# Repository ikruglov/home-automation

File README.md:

# Home automation · hardware & firmware

PCBs and ESPHome configurations for connecting existing appliances to Home Assistant.

Project records covering PCB design, firmware integration, and assembled hardware.

<table>
<tr>
<td width="45%">

</td>
<td valign="top">
<strong><a href="esp32-ap7921/">APC AP7921 controller retrofit</a></strong><br>
An installed and working replacement controller bringing eight-outlet control and monitoring into Home Assistant. An internal board swap retains the enclosure, outlet hardware, and front-panel layout.<br><br>
<sub>Four-layer PCB · ESP32-C6 · CH390H Ethernet · ESPHome</sub>
</td>
</tr>
<tr>
<td align="center">
<br>
<sub>PCB layout · Work in progress</sub>
</td>
<td valign="top">
<strong><a href="esp32-water-meter/">Water-meter reader</a></strong><br>
An ESP32-C6 water-meter reader with 18650 backup power to keep counting through USB power interruptions. Two sensor inputs support a planned approach to rejecting false counts from small target movements. Assembled and tested; current firmware uses Wi-Fi and one sensor.<br><br>
<sub>PCB design · ESP32-C6 · ESPHome · Battery backup · Dual sensor inputs</sub>
</td>
</tr>
<tr>
<td>

</td>
<td valign="top">
<strong><a href="esp32-create-ceiling-fan-tuya/">Create ceiling-fan retrofit</a></strong><br>
A replacement PCB with an ESP32-C3 module, support components, and programming connections, fitted to the original fan controller. ESPHome provides fan and light control over Tuya UART.<br><br>
<sub>PCB design · ESP32-C3 · Wi-Fi · Tuya UART</sub>
</td>
</tr>
<tr>
<td>

</td>
<td valign="top">
<strong><a href="esp32-climarad-v2x/">Climarad ventilation interface</a></strong><br>
A carrier PCB connecting existing Ethernet/PoE and isolated RS485 modules, with a printed enclosure and Modbus integration for Home Assistant.<br><br>
<sub>Carrier PCB · ESP32-S3 · Ethernet / PoE · RS485 / Modbus</sub>
</td>
</tr>
</table>

## Design decisions

| Project | Requirement | Approach | Boundary |
|---|---|---|---|
| AP7921 retrofit | Replace the controller and integrate outlet control and monitoring into Home Assistant | Four-layer controller PCB and ESPHome firmware, fitted to the existing enclosure and front panel | AP7921 mounting points and front-panel openings; USB-C replaces the serial connector |
| Water-meter reader (in progress) | Keep counting through power interruptions and reject false counts at the detection boundary | 18650 backup, two sensor inputs, and ESP32-C6 with a future Zigbee option | Assembled and tested; current firmware uses one sensor and Wi-Fi |
| Ceiling-fan retrofit | Expose the existing fan and light controls in Home Assistant | A custom ESP32-C3 board replaces the Wi-Fi interface and communicates with the retained controller over Tuya UART | Board fit and datapoint mappings are specific to the controller shown |
| Climarad interface | Connect ventilation controls and measurements to Home Assistant; power the interface through PoE | A custom carrier PCB combines Ethernet/PoE and isolated RS485 modules; ESPHome maps Modbus registers into entities | Uses the unit's Modbus interface and requires its device address |

All four projects use ESPHome's firmware framework and protocol components. The Climarad interface uses Waveshare modules for its ESP32, PoE, and isolated RS485 functions.

## Explore the projects

| Project | Hardware | Firmware | Additional material |
|---|---|---|---|
| [APC AP7921](esp32-ap7921/) | [Four-layer controller overview](esp32-ap7921/#four-layer-controller-pcb) | [ESPHome configuration and components](esp32-ap7921/firmware/) | [Installed retrofit](esp32-ap7921/#board-swap-retrofit) · [USB-C insert STL](esp32-ap7921/usb-c-insert.stl) |
| [Water-meter reader](esp32-water-meter/) | [KiCad design](esp32-water-meter/hardware/) | [ESPHome configuration](esp32-water-meter/firmware/) | [Case STL models](esp32-water-meter/case/) · [Development status](esp32-water-meter/#development-status) |
| [Create ceiling fan](esp32-create-ceiling-fan-tuya/) | [KiCad design](esp32-create-ceiling-fan-tuya/kicad/) | [ESPHome configuration](esp32-create-ceiling-fan-tuya/esphome.yaml) | [BOM](esp32-create-ceiling-fan-tuya/#bill-of-materials) · [Build gallery](esp32-create-ceiling-fan-tuya/#build-gallery) |
| [Climarad Sensa V2X](esp32-climarad-v2x/) | [KiCad design](esp32-climarad-v2x/kicad/) | [ESPHome configuration](esp32-climarad-v2x/esphome.yaml) | [Printable enclosure](esp32-climarad-v2x/case.3mf) |

These are hardware-specific project records. Read the compatibility and configuration notes before adapting a design to another appliance.

## License

- **Design files, documentation, and photographs:** [CC BY-NC 4.0](LICENSES/CC-BY-NC-4.0.txt).
- **Software and ESPHome configurations:** [PolyForm Noncommercial 1.0.0](LICENSES/PolyForm-Noncommercial-1.0.0.txt).

See [LICENSE](LICENSE) for scope.

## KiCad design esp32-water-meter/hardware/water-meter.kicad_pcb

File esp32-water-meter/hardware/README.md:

# Water-meter hardware

Open `water-meter.kicad_pro` with **KiCad 10** and matching standard libraries.
The schematic and PCB use file-format versions `20260306` and `20260206`.

Included:

- Schematic, PCB layout, and project settings.
- Project-local FS8205A and JLCImport symbols used by this design.
- Three JLCImport footprints and their referenced 3D models.
- Project-relative library tables and model paths.

The design also references **Espressif's `PCM_Espressif` library** for the
ESP32-C6 module. Install that library separately for library-based editing and
updates; placed symbols and footprints are embedded in the design files. Its
3D model currently uses the original `KICAD8_3RD_PARTY` variable. Configure that
variable for the installed library location, or update the model path locally.
Standard models use `KICAD10_3DMODEL_DIR`.

This export changes local library/model paths, not the circuit or routing.
The custom symbol library contains only the symbols needed here; unrelated
private-project libraries are excluded. Production outputs and editor state
are not included.

## Open work

The private design's TODO still lists **F1 value/selection** as unresolved.
The firmware development notes describe modifications to the sensor input
and USB power handling; reconcile those with the assembled revision before
using these files to build another board.

KiCad ERC/DRC and schematic-to-PCB agreement have not been checked for this
export. Regenerate manufacturing outputs only after reviewing the design.

## Protection-circuit references

The PCB's stored pad nets place Q6 (AO3401A, LCSC C347476) in the battery
positive connection, with its gate referenced to BAT−: the intended reverse
insertion protection stage. Q1 is a separate MOSFET in the USB/battery power
path. See the [Q6 datasheet](https://www.lcsc.com/datasheet/C347476.pdf).

U5 is labelled DW01A in the schematic and carries LCSC C686633. Its OD/OC
outputs drive Q5, the dual battery-disconnect MOSFET. The
[datasheet linked to C686633](https://www.lcsc.com/datasheet/C686633.pdf)
identifies the part as DW01 and documents overcharge, overdischarge,
overcurrent, and short-circuit detection. Confirm the fitted variant before
relying on specific thresholds; no thresholds are claimed on the project page.

F1 is a resettable fuse in the battery-positive path. USBLC6 protection and
SMAJ12A TVS devices are also present at the external interfaces/sensor supply.
Protection functions are identified from the design; fault performance has not
been independently verified for this export.

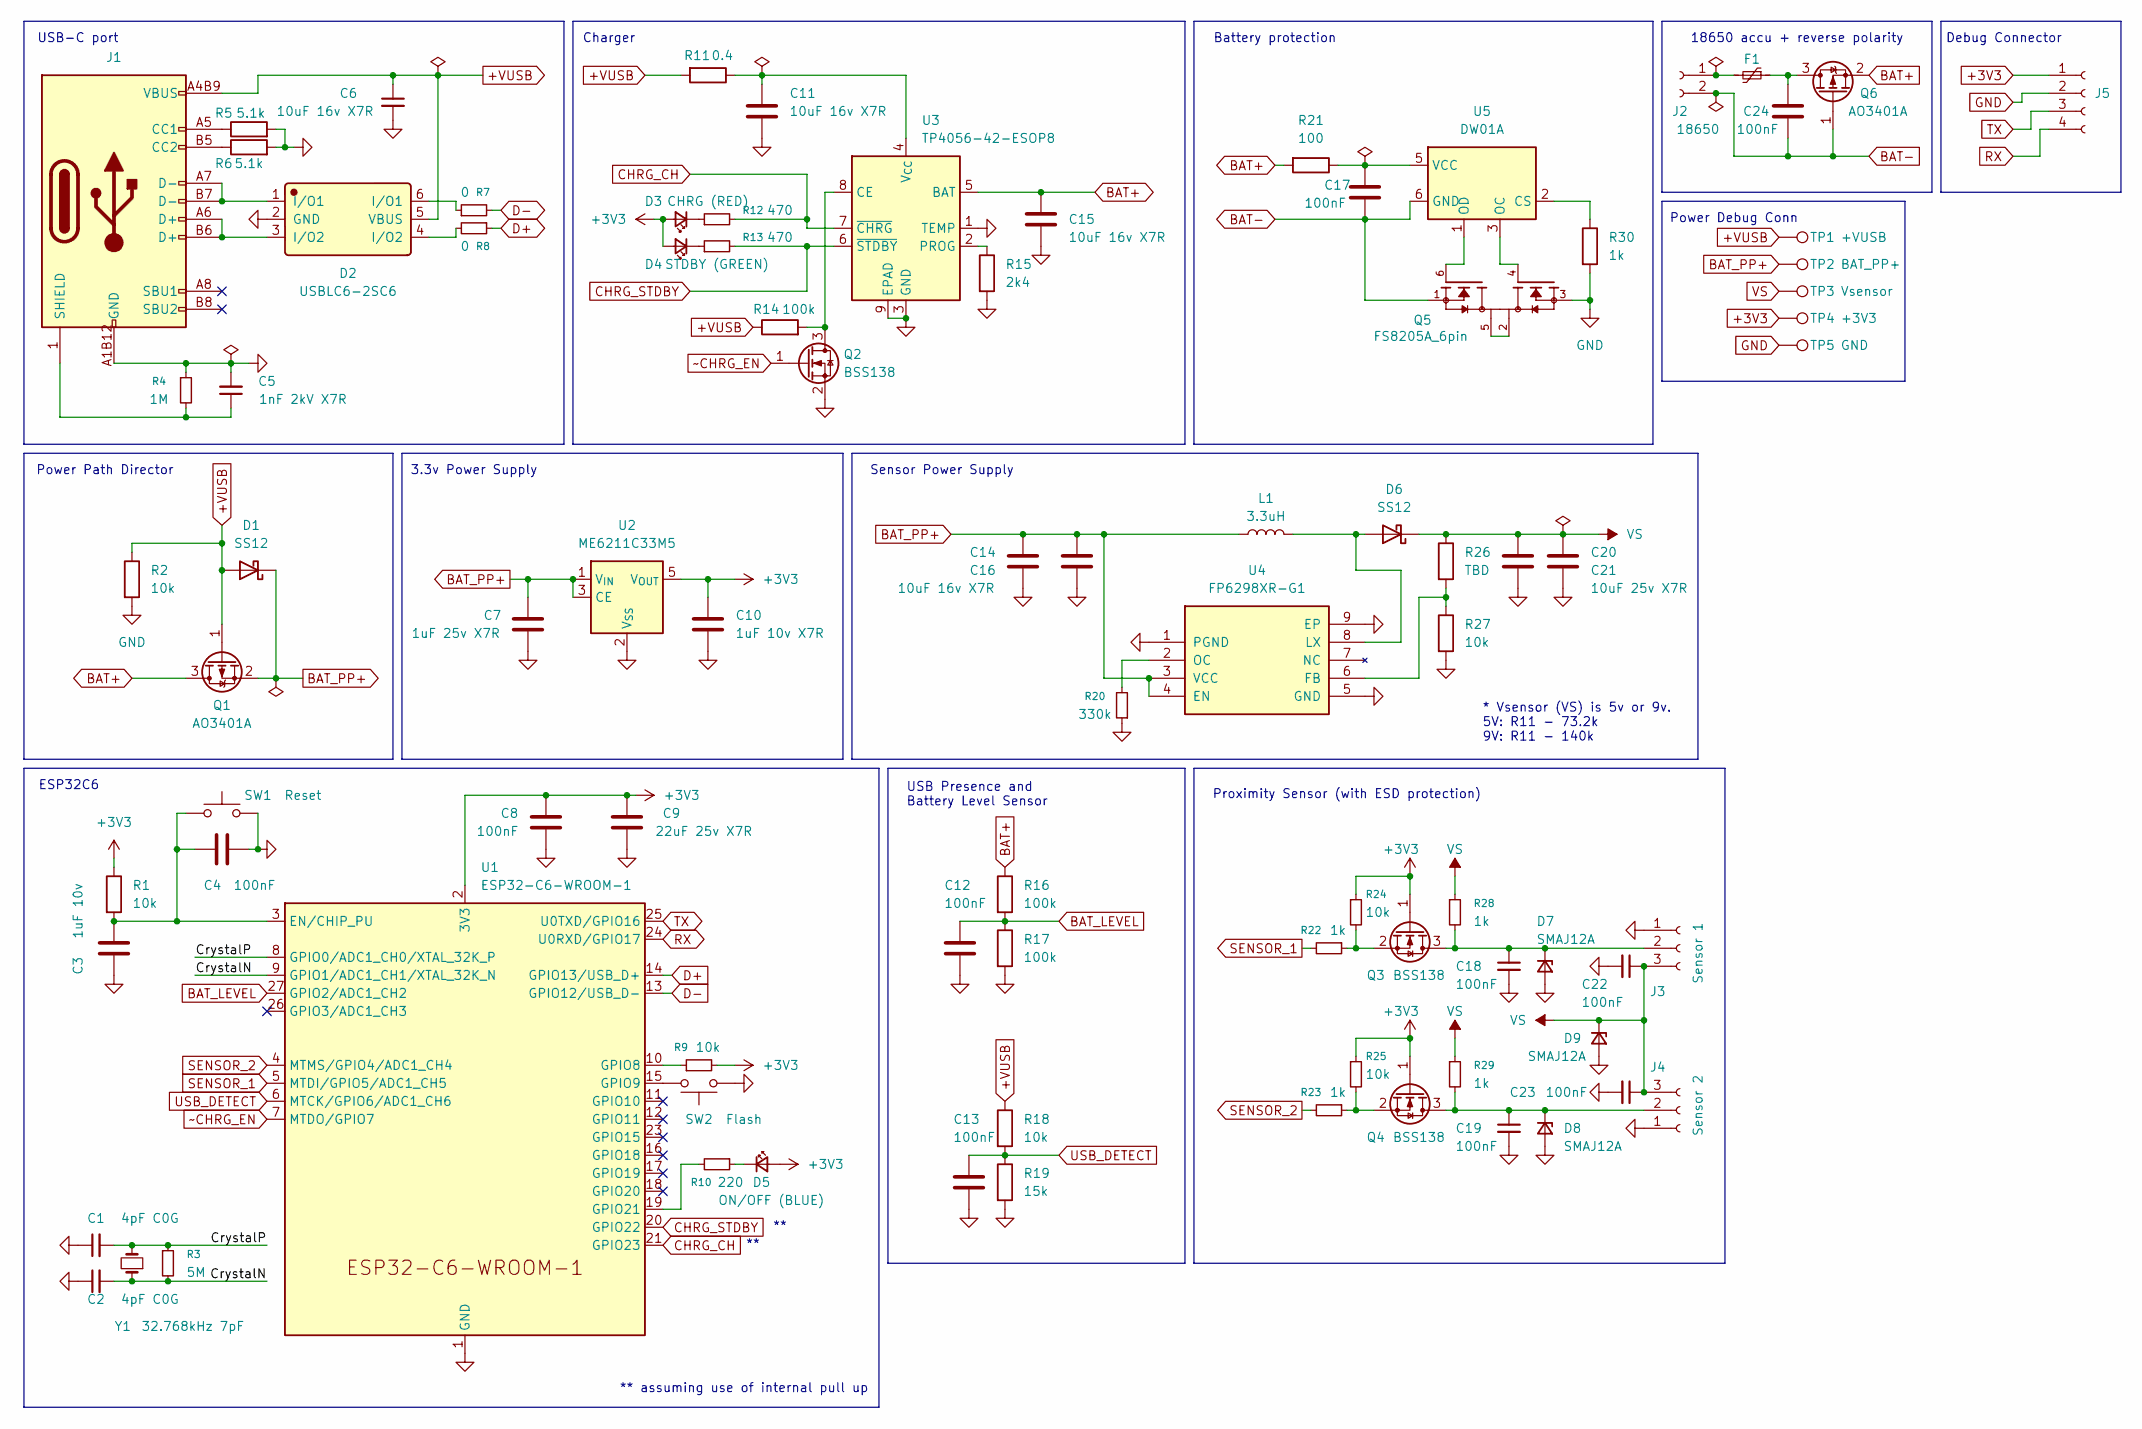
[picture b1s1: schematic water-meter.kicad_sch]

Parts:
C1, C2: 4pF C0G; C_0805_2012Metric_Pad1.18x1.45mm_HandSolder
C3: 1uF 10v; C_0805_2012Metric_Pad1.18x1.45mm_HandSolder
C4, C8, C12, C13, C17, C18, C19, C22, C23, C24: 100nF; C_0805_2012Metric_Pad1.18x1.45mm_HandSolder
C5: 1nF 2kV X7R; C_1206_3216Metric_Pad1.33x1.80mm_HandSolder; LCSC C16196254
C6, C11, C14, C15, C16: 10uF 16v X7R; C_0805_2012Metric_Pad1.18x1.45mm_HandSolder; LCSC C95841
C7: 1uF 25v X7R; C_0805_2012Metric_Pad1.18x1.45mm_HandSolder; LCSC C116352
C9: 22uF 25v X7R; C_1210_3225Metric_Pad1.33x2.70mm_HandSolder; LCSC C21397
C10: 1uF 10v X7R; C_0805_2012Metric_Pad1.18x1.45mm_HandSolder
C20, C21: 10uF 25v X7R; C_1206_3216Metric_Pad1.33x1.80mm_HandSolder; LCSC C77093
D1: SS12; D_SMA_Handsoldering; LCSC C2479
D2: USBLC6-2SC6; SOT-23-6_Handsoldering; Manufacturer Part USBLC6-2SC6; LCSC C2687116
D3: CHRG (RED); LED_0805_2012Metric_Pad1.15x1.40mm_HandSolder
D4: STDBY (GREEN); LED_0805_2012Metric_Pad1.15x1.40mm_HandSolder
D5: ON/OFF (BLUE); LED_0805_2012Metric_Pad1.15x1.40mm_HandSolder
D6: SS12; D_SMA; LCSC C2479
D7, D8, D9: SMAJ12A; D_SMA_Handsoldering; LCSC C113957
F1: MF-USMF150-2; Fuse_1210_3225Metric_Pad1.42x2.65mm_HandSolder; LCSC C2153943
J1: TYPE-C-31-M-12; LCSC C165948
J2: 18650; BatteryHolder_MPD_BH-18650-PC
J3: Sensor 1; JST_XH_B3B-XH-A_1x03_P2.50mm_Vertical
J4: Sensor 2; JST_XH_B3B-XH-A_1x03_P2.50mm_Vertical
J5: Conn_01x04_Socket; PinHeader_1x04_P2.54mm_Vertical
L1: 3.3uH; L_7.3x7.3_H3.5; LCSC C167219
Q1, Q6: AO3401A; SOT-23_Handsoldering; LCSC C347476
Q2, Q3, Q4: BSS138; SOT-23_Handsoldering; LCSC C427380
Q5: FS8205A_6pin; SOT-23-6_Handsoldering; LCSC C351449
R1, R2, R9, R18, R24, R25, R27: 10k; R_0805_2012Metric_Pad1.20x1.40mm_HandSolder
R3: 5M; R_0805_2012Metric_Pad1.20x1.40mm_HandSolder
R4: 1M; R_0805_2012Metric_Pad1.20x1.40mm_HandSolder
R5, R6: 5.1k; R_0805_2012Metric_Pad1.20x1.40mm_HandSolder
R7, R8: 0; R_0805_2012Metric_Pad1.20x1.40mm_HandSolder
R10: 220; R_0805_2012Metric_Pad1.20x1.40mm_HandSolder
R11: 0.4; R_1206_3216Metric_Pad1.30x1.75mm_HandSolder; LCSC C7421619
R12, R13: 470; R_0805_2012Metric_Pad1.20x1.40mm_HandSolder
R14, R16, R17: 100k; R_0805_2012Metric_Pad1.20x1.40mm_HandSolder
R15: 2k4; R_0805_2012Metric_Pad1.20x1.40mm_HandSolder
R19: 15k; R_0805_2012Metric_Pad1.20x1.40mm_HandSolder
R20: 330k; R_0805_2012Metric_Pad1.20x1.40mm_HandSolder
R21: 100; R_0805_2012Metric_Pad1.20x1.40mm_HandSolder
R22, R23, R28, R29, R30: 1k; R_0805_2012Metric_Pad1.20x1.40mm_HandSolder
R26: TBD; R_0805_2012Metric_Pad1.20x1.40mm_HandSolder
SW1: Reset; SW_SPST_TS-1088-xR025
SW2: Flash; SW_SPST_TS-1088-xR025
TP1: +VUSB; TestPoint_Pad_D1.5mm
TP2: BAT_PP+; TestPoint_Pad_D1.5mm
TP3: Vsensor; TestPoint_Pad_D1.5mm
TP4: +3V3; TestPoint_Pad_D1.5mm
TP5: GND; TestPoint_Pad_D1.5mm
U1: ESP32-C6-WROOM-1
U2: ME6211C33M5; SOT-23-5_HandSoldering; LCSC C82942
U3: TP4056-42-ESOP8; SOIC-8-1EP_3.9x4.9mm_P1.27mm_EP2.41x3.3mm_ThermalVias; LCSC C725790
U4: FP6298XR-G1; SOIC-8-1EP_3.9x4.9mm_P1.27mm_EP2.29x3mm_ThermalVias; Manufacturer Part FP6298XR-G1; LCSC C88319
U5: DW01A; SOT-23-6_Handsoldering; LCSC C686633
Y1: 32.768kHz 7pF; Crystal_SMD_3215-2Pin_3.2x1.5mm; LCSC C41349296

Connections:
+3V3: C8.1, C9.1, C10.1, D3.2 (A), D4.2 (A), D5.2 (A), J5.1, Q3.1 (G), Q4.1 (G), R1.1, R9.2, R24.1, R25.1, TP4.1 (1_1), U1.2 (3V3), U2.5 (V_{OUT})
+VUSB: C6.1, D1.2 (A), D2.5 (VBUS), J1.A4B9 (VBUS), J1.B4A9 (VBUS), Q1.1 (G), R2.1, R11.2, R14.1, R18.1, TP1.1 (1_1)
/CrystalN: C2.2, R3.2, U1.9 (GPIO1/ADC1_CH1/XTAL_32K_N), Y1.1
/CrystalP: C1.2, R3.1, U1.8 (GPIO0/ADC1_CH0/XTAL_32K_P), Y1.2
BAT+: C15.1, Q1.3 (D), Q6.2 (S), R16.1, R21.2, U3.5 (BAT)
BAT-: C17.2, C24.1, J2.2, Q5.1, Q6.1 (G), U5.6 (GND)
BAT_LEVEL: C12.1, R16.2, R17.1, U1.27 (GPIO2/ADC1_CH2)
BAT_PP+: C7.1, C14.1, C16.1, D1.1 (K), L1.1, Q1.2 (S), TP2.1 (1_1), U2.1 (V_{IN}), U2.3 (CE), U4.3 (VCC), U4.4 (EN)
CHRG_CH: R12.2, U1.21 (GPIO23), U3.7 (~CHRG)
CHRG_STDBY: R13.2, U1.20 (GPIO22), U3.6 (~STDBY)
D+: R8.1, U1.14 (GPIO13/USB_D+)
D-: R7.2, U1.13 (GPIO12/USB_D-)
GND: C1.1, C2.1, C3.2, C4.2, C5.2, C6.2, C7.2, C8.2, C9.2, C10.2, C11.1, C12.2, C13.2, C14.2, C15.2, C16.2, C18.2, C19.2, C20.2, C21.2, C22.2, C23.2, D2.2 (GND), D7.2 (A), D8.2 (A), D9.2 (A), J1.A1B12 (GND), J1.B1A12 (GND), J3.1, J4.1, J5.2, Q2.2 (S), Q5.3, R2.2, R4.1, R5.2, R6.2, R15.2, R17.2, R19.2, R20.1, R27.2, R30.2, SW1.1, SW2.1, TP5.1 (1_1), U1.1 (GND), U1.28 (GND), U1.29 (GND), U2.2 (V_{SS}), U3.1 (TEMP), U3.3 (GND), U3.9 (EPAD), U4.1 (PGND), U4.5 (GND), U4.9 (EP)
unnamed: D2.1 (I/O1), J1.A7 (D-), J1.B7 (D-)
unnamed: D2.6 (I/O1), R7.1
unnamed: D2.3 (I/O2), J1.A6 (D+), J1.B6 (D+)
unnamed: D2.4 (I/O2), R8.2
unnamed: D3.1 (K), R12.1
unnamed: D4.1 (K), R13.1
unnamed: D5.1 (K), R10.1
unnamed: D6.2 (A), L1.2, U4.8 (LX)
unnamed: C18.1, D7.1 (K), J3.2, Q3.3 (D), R28.2
unnamed: C19.1, D8.1 (K), J4.2, Q4.3 (D), R29.2
unnamed: J1.A5 (CC1), R5.1
unnamed: J1.B5 (CC2), R6.1
unnamed: C5.1, J1.1 (SHIELD), R4.2
unnamed: F1.2, J2.1
unnamed: Q2.3 (D), R14.2, U3.8 (CE)
unnamed: Q3.2 (S), R22.1, R24.2
unnamed: Q4.2 (S), R23.1, R25.2
unnamed: Q5.2, Q5.5
unnamed: C24.2, F1.1, Q6.3 (D)
unnamed: C3.1, C4.1, R1.2, SW1.2, U1.3 (EN/CHIP_PU)
unnamed: R9.1, U1.10 (GPIO8)
unnamed: SW2.2, U1.15 (GPIO9)
unnamed: R10.2, U1.19 (GPIO21)
unnamed: R15.1, U3.2 (PROG)
unnamed: C11.2, R11.1, U3.4 (V_{CC})
unnamed: R26.2, R27.1, U4.6 (FB)
unnamed: R20.2, U4.2 (OC)
unnamed: R30.1, U5.2 (CS)
unnamed: Q5.4, U5.3 (OC)
unnamed: Q5.6, U5.1 (OD)
unnamed: C17.1, R21.1, U5.5 (VCC)
RX: J5.4, U1.24 (U0RXD/GPIO17)
SENSOR_1: R22.2, U1.5 (MTDI/GPIO5/ADC1_CH5)
SENSOR_2: R23.2, U1.4 (MTMS/GPIO4/ADC1_CH4)
TX: J5.3, U1.25 (U0TXD/GPIO16)
USB_DETECT: C13.1, R18.2, R19.1, U1.6 (MTCK/GPIO6/ADC1_CH6)
VS: C20.1, C21.1, C22.1, C23.1, D6.1 (K), D9.1 (K), J3.3, J4.3, R26.1, R28.1, R29.1, TP3.1 (1_1)
~CHRG_EN: Q2.1 (G), U1.7 (MTDO/GPIO7)

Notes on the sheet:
USB Presence and Battery Level Sensor
USB-C port
18650 accu + reverse polarity
* Vsensor (VS) is 5v or 9v. 5V: R11 - 73.2k 9V: R11 - 140k
3.3v Power Supply
ESP32C6
** assuming use of internal pull up
Power Debug Conn
Proximity Sensor (with ESD protection)
Debug Connector
Battery protection
Power Path Director
Sensor Power Supply
Charger

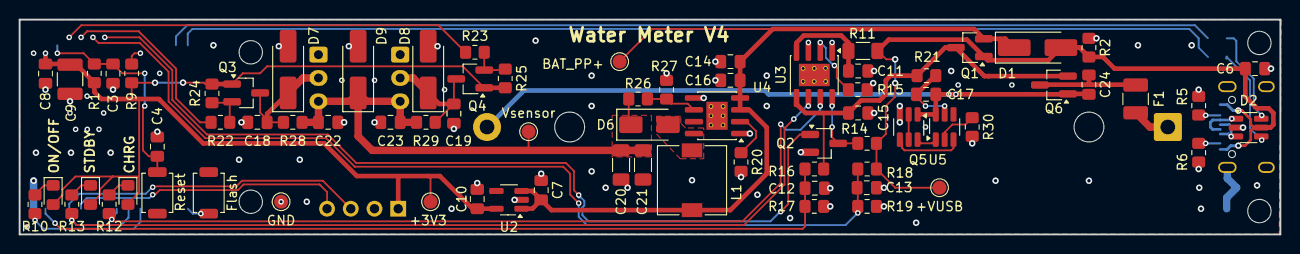
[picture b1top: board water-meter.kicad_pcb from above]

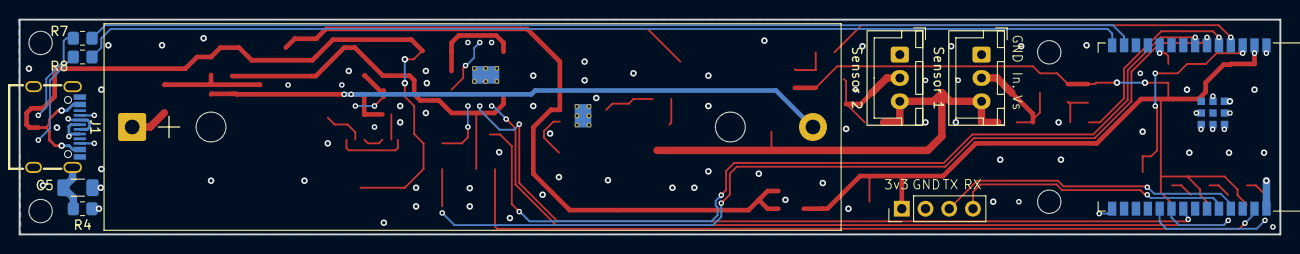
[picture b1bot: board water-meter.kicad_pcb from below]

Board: 2 copper layers, 135.0 x 23.0 mm, 85 parts (10 on the bottom side), 49 nets.

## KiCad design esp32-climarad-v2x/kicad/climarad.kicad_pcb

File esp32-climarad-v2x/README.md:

[← All projects](../README.md)

# Climarad ventilation interface

**A PoE-powered ESPHome interface for bringing a Climarad Sensa V2X ventilation unit into Home Assistant over Modbus.**

*The assembled carrier board, with the Ethernet/PoE and RS485 modules fitted.*

## Design

The interface connects a [Climarad Sensa V2X ventilation unit](https://www.climarad.nl/en/products/climarad-sensa-v2x/) to Home Assistant, using PoE for power.

A carrier PCB brings together a Waveshare [ESP32-S3 Ethernet board with PoE](https://www.waveshare.com/esp32-s3-eth.htm?sku=28771) and an [isolated TTL-to-RS485 module](https://www.waveshare.com/ttl-to-rs485-c.htm). The ESPHome configuration maps the ventilation unit's Modbus registers into sensors and controls. A printable enclosure is included with the design.

Modbus communication uses ESPHome's [Modbus Controller component](https://esphome.io/components/modbus_controller/).

## Carrier PCB

The board provides module mounting and interconnection between the ESP32-S3 board, isolated RS485 module, and Modbus connector. The Ethernet/PoE and RS485 circuitry resides on the modules; the carrier layout focuses on their placement and connections.

*Front and back carrier-board layouts. Select either image for full resolution.*

[PCB source](kicad/climarad.kicad_pcb) · [Schematic source](kicad/climarad.kicad_sch) · [KiCad project](kicad/climarad.kicad_pro)

<details>
<summary>View the schematic</summary>

</details>

### Enclosure

[Printable enclosure](case.3mf)

## System overview

```mermaid
flowchart LR
    HA[Home Assistant] <-->|Ethernet / ESPHome API| ESP[ESP32-S3 + W5500]
    POE[PoE supply] -->|Power| ESP
    ESP <-->|UART| RS[Isolated RS485 module]
    RS <-->|Modbus RTU| V[Climarad Sensa V2X]
```

The custom PCB carries the ESP32 and RS485 modules. Choosing a PoE-capable module addressed the power requirement while keeping the board focused on interconnection. The published configuration uses Ethernet for Home Assistant communication and a separate UART for Modbus.

## Published firmware capabilities

The [ESPHome configuration](esphome.yaml) defines:

| Area | Entities |
|---|---|
| Air measurements | CO₂, humidity, temperature |
| Diagnostics | Supply/exhaust fan speed, current mode, decoded error flags, desired CO₂, filter-reset count |
| Controls | Operating mode, desired CO₂ level, child lock, window-ventilation setting |
| Adjustment | CO₂ compensation, LED brightness |

Measurement conversion and filtering are explicit in the YAML: humidity and temperature registers are scaled, and CO₂ values `0` and `32767` are filtered out. These details can be inspected alongside the register addresses and mode mappings.

## Sources and configuration

| File | Contents |
|---|---|
| [esphome.yaml](esphome.yaml) | Ethernet, Modbus register mappings, sensors, and controls |
| [kicad/](kicad/) | Schematic, PCB layout, and KiCad project |
| [case.3mf](case.3mf) | Printable enclosure |

This project targets a Sensa V2X with its Modbus interface. In `esphome.yaml`, replace the placeholder Modbus address `000` with the address for your unit; the configuration notes identify the Modbus module cable as the place to find it. Review device naming, API encryption, and OTA authentication for your installation.

The photographs document the assembled board and enclosure. The repository does not include runtime measurement logs or a compatibility test matrix for other Climarad models.

## Build gallery

<details>
<summary>More assembly and enclosure photographs</summary>

</details>

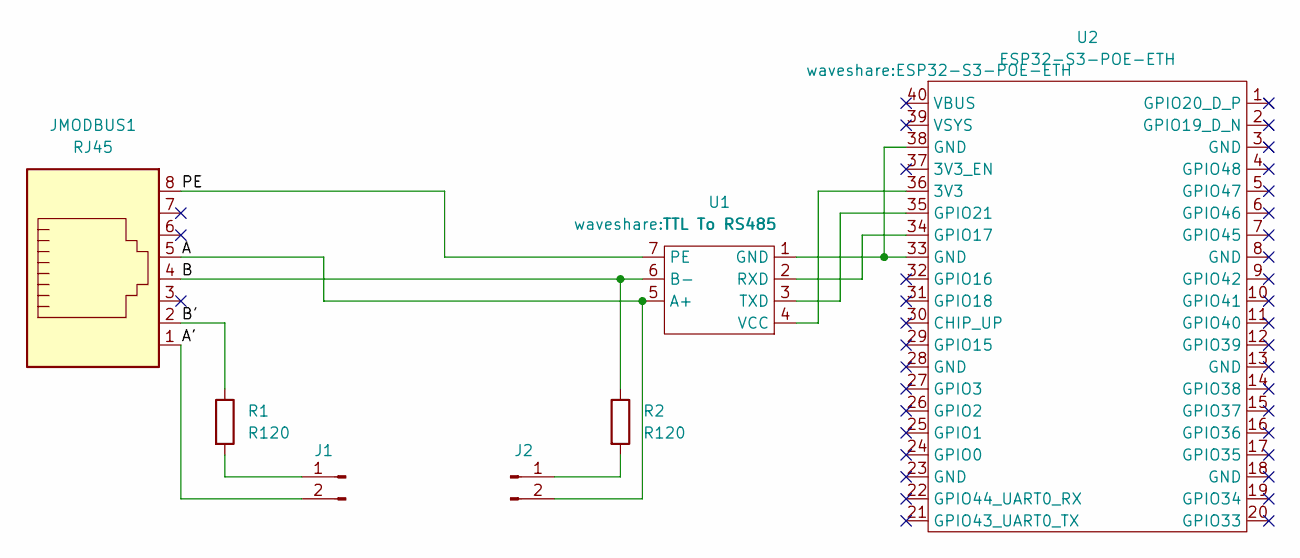
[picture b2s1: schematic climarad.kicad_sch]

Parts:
J1, J2: Conn_01x02_Pin; PinHeader_1x02_P2.54mm_Vertical
JMODBUS1: RJ45; RJ45_Amphenol_54602-x08_Horizontal
R1, R2: R120; R_0805_2012Metric
U1: TTL To RS485
U2: ESP32-S3-POE-ETH

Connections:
/A: J2.2, JMODBUS1.5, U1.5 (A+)
/A': J1.2, JMODBUS1.1
/B: JMODBUS1.4, R2.1, U1.6 (B-)
/B': JMODBUS1.2, R1.1
/PE: JMODBUS1.8, U1.7 (PE)
unnamed: J1.1, R1.2
unnamed: J2.1, R2.2
unnamed: U1.1 (GND), U2.33 (GND), U2.38 (GND)
unnamed: U1.2 (RXD), U2.34 (GPIO17)
unnamed: U1.3 (TXD), U2.35 (GPIO21)
unnamed: U1.4 (VCC), U2.36 (3V3)

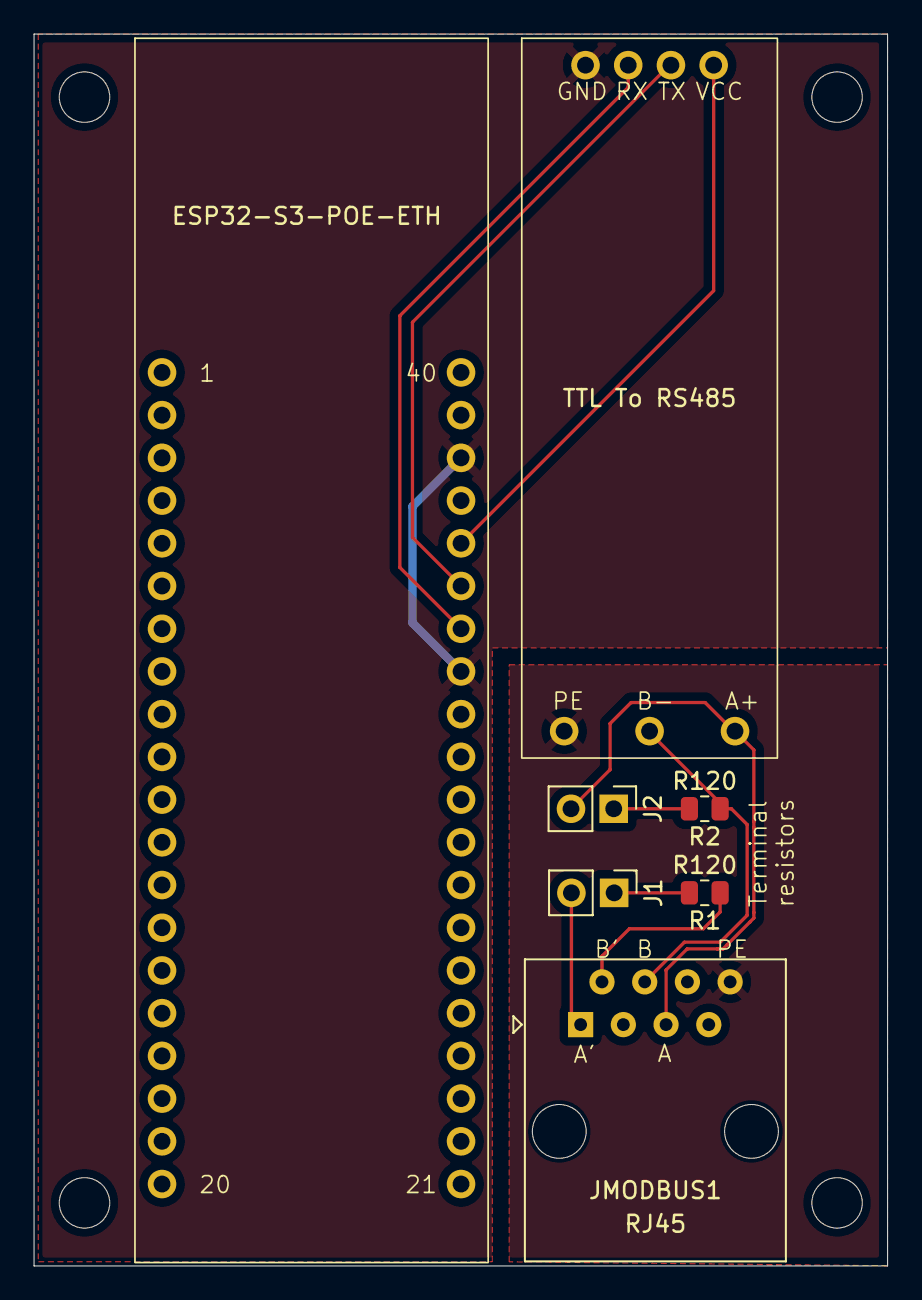
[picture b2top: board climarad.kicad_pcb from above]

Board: 2 copper layers, 50.8 x 73.2 mm, 7 parts (0 on the bottom side), 11 nets.

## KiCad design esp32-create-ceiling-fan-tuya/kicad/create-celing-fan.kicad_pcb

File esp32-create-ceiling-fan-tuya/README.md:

[← All projects](../README.md)

# Create ceiling-fan retrofit

**A custom ESP32-C3 interface board and ESPHome configuration for fan and light control in Home Assistant.**

*The assembled replacement board, front and back.*

## Design

The PCB replaces the WBR3 Wi-Fi module and associated daughterboard arrangement in the [Create ceiling fan](https://www.create-store.com/uk/2401-buy-ceiling-fans) shown below. The replacement uses an ESP32-C3 running ESPHome and communicates with the existing appliance controller through the Tuya UART protocol.

The fan's existing controller remains responsible for appliance control; ESPHome provides the [Tuya MCU protocol component](https://esphome.io/components/tuya/).

## PCB design

The replacement board combines the ESP32-C3 module, support components, flash/reset buttons, and programming connections in the footprint shown below. Components and routing occupy both sides of the board; the module's antenna area is marked at the top of the layout.

*Front and back layout views. Select either image for full resolution.*

[PCB source](kicad/create-celing-fan.kicad_pcb) · [Schematic source](kicad/create-celing-fan.kicad_sch) · [KiCad project](kicad/create-celing-fan.kicad_pro) · [BOM](#bill-of-materials)

<details>
<summary>View the schematic</summary>

</details>

### Fit in the original controller

*The replacement interface board fitted to the existing controller assembly. The board outline and connection positions need to suit this hardware; the original motor and light controller remains in place.*

## Bill of materials

- [Assembly BOM (CSV)](bom.csv) — manufacturers, part numbers, quantities, and footprints.
- [KiCad BOM export (CSV)](kicad/create-celing-fan.csv) — references, quantities, values, and footprints matching the published PCB.

The assembled board used capacitors, resistors, and buttons from assortment kits. The assembly BOM reconstructs suitable part selections rather than an exact record of every fitted part; confirm substitutions and footprints before ordering assembly.

## System overview

```mermaid
flowchart LR
    HA[Home Assistant] <-->|Wi-Fi / ESPHome API| ESP[Custom ESP32-C3 board]
    ESP <-->|Tuya UART · 9600 baud| MCU[Existing fan controller]
    MCU --> FAN[Fan]
    MCU --> LIGHT[Light]
```

The published configuration disables UART logging to leave that serial interface available for communication with the fan controller. Fan and light entities use `ALWAYS_OFF` as their configured restore mode.

## Flashing and first boot

The programming connection and Tuya communication share **GPIO20 (ESP RX) and GPIO21 (ESP TX)**. During flashing they connect to the USB–UART adapter; in normal operation they communicate with the fan controller.

Flash the replacement board separately from the mains-powered controller, using a suitable 3.3 V supply and 3.3 V UART logic.

| USB–UART adapter | Replacement board |
|---|---|
| TX | RX / GPIO20 |
| RX | TX / GPIO21 |
| GND | GND |

1. Fit the **Flash jumper**, then press and release **Reset** to enter download mode.
2. Flash the firmware.
3. Remove the Flash jumper and disconnect the adapter's TX/RX leads before normal operation. Reset to boot the firmware.
4. With power disconnected, install the replacement board in the matching controller. Verify operation through Wi-Fi/Home Assistant.

The header's **EN-labelled contact is not connected to the ESP reset circuit in this design**; do not use it as an RTS auto-reset connection. Use the board's Reset control. See the [project flashing discussion](https://github.com/ikruglov/home-automation/issues/2#issuecomment-4596481200) and [Espressif's download-mode documentation](https://docs.espressif.com/projects/esptool/en/latest/esp32c3/advanced-topics/boot-mode-selection.html).

### Repeated resets after a successful flash

In [issue #2](https://github.com/ikruglov/home-automation/issues/2), a builder flashed successfully but then saw repeated resets while connected through a laptop dock. The board came online after moving the adapter to a power-only USB source; it also came online when fitted to the powered controller. The fan itself had not yet been connected in that report.

Shared-UART interference was the suspected explanation: after boot, those pins carry Tuya traffic rather than a programming session. However, power and USB data conditions changed together, so the report does not isolate the reset cause. Disconnect the programmer's TX/RX for normal operation and check the power supply if resets continue. Keep `logger.baud_rate: 0`, as configured, to avoid injecting log messages into the Tuya UART. [ESPHome logger documentation](https://esphome.io/components/logger/#configuration-variables)

## Published firmware capabilities

The [ESPHome configuration](esphome.yaml) maps the following Tuya datapoints:

| Function | Datapoint(s) | Configuration |
|---|---|---|
| Fan | 60, 62, 63 | On/off, six speed levels, direction |
| Light | 20, 22 | On/off and brightness |

It also exposes connection status, Wi-Fi signal, uptime, and a restart button. Color-temperature settings are commented out in the published YAML and are not presented here as an implemented feature.

## Compatibility and sources

**Match the controller hardware, not just the fan's product name.** This project was developed for a fan that already had Wi-Fi. The original project notes identify different controller modules sold under the same Create model name; compare your hardware with the original-board photographs below.

| File | Contents |
|---|---|
| [esphome.yaml](esphome.yaml) | ESP32-C3 configuration and Tuya datapoint mappings |
| [kicad/](kicad/) | Schematic, PCB layout, KiCad project, and component CSV |

Before adapting the configuration, replace the `XXX` Wi-Fi placeholders and review device naming, API encryption, and OTA authentication. GPIO assignments and datapoint mappings describe the hardware shown here.

The photographs document assembly and fitment to the original controller. They do not establish compatibility with other controller revisions.

## Build gallery

<details>
<summary>Additional installation photograph</summary>

</details>

### Original hardware

<details>
<summary>Original board and installation — compare these before adapting the design</summary>

The original photographed assembly does not have a separate 5 V ↔ 3.3 V logic daughterboard.

</details>

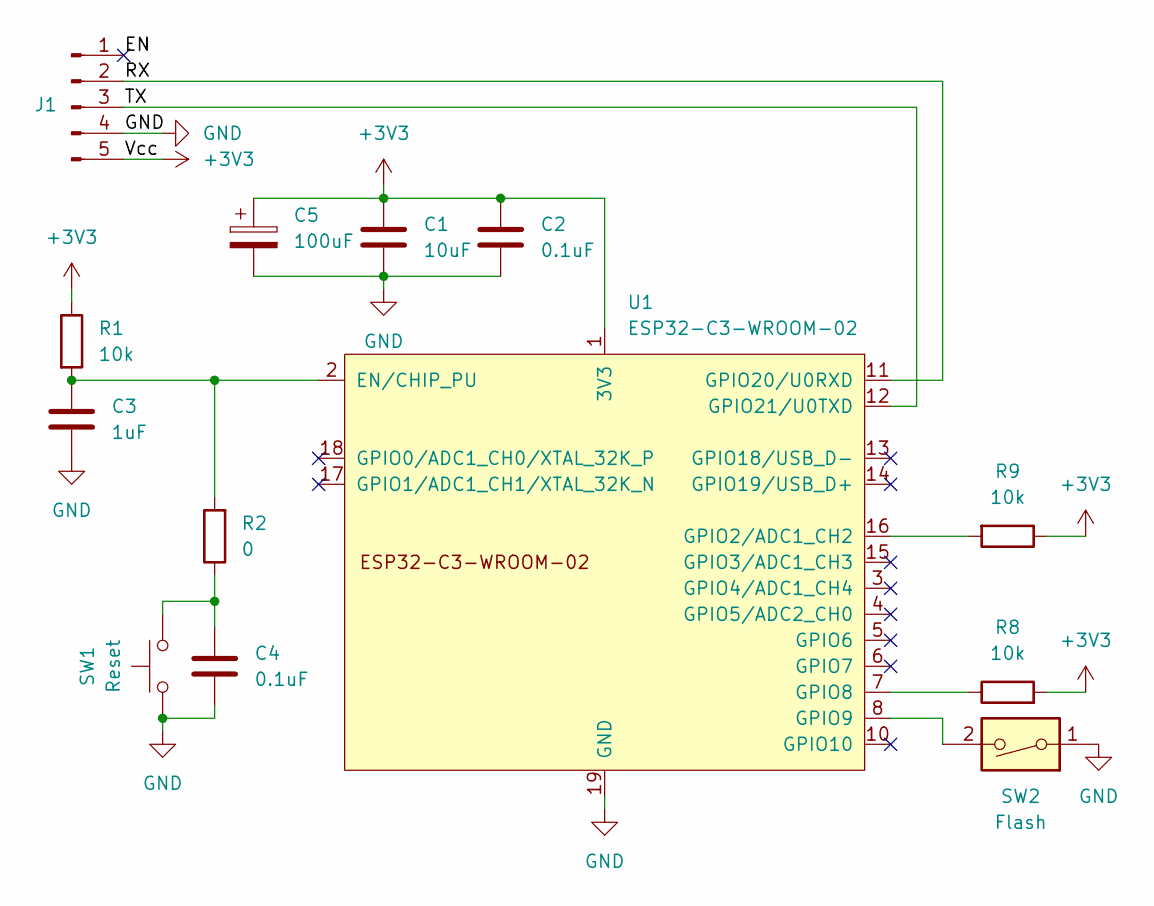
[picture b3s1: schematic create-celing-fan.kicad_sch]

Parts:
C1: 10uF; C_0805_2012Metric
C2, C4: 0.1uF; C_0805_2012Metric
C3: 1uF; C_0805_2012Metric
C5: 100uF; CP_Elec_5x5.4
J1: Conn_01x05_Pin; PinHeader_1x05_P2.54mm_Vertical
R1, R8, R9: 10k; R_0805_2012Metric
R2: 0; R_0805_2012Metric
SW1: Reset; SW_Push_1P1T_XKB_TS-1187A
SW2: Flash; PinHeader_1x02_P2.54mm_Horizontal
U1: ESP32-C3-WROOM-02

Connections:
+3V3: C1.1, C2.1, C5.1, J1.5, R1.1, R8.2, R9.1, U1.1 (3V3)
/EN: J1.1
/RX: J1.2, U1.11 (GPIO20/U0RXD)
/TX: J1.3, U1.12 (GPIO21/U0TXD)
GND: C1.2, C2.2, C3.2, C4.2, C5.2, J1.4, SW1.1, SW2.1, U1.9 (GND), U1.19 (GND)
unnamed: C4.1, R2.1, SW1.2
unnamed: C3.1, R1.2, R2.2, U1.2 (EN/CHIP_PU)
unnamed: R9.2, U1.16 (GPIO2/ADC1_CH2)
unnamed: R8.1, U1.7 (GPIO8)
unnamed: SW2.2, U1.8 (GPIO9)

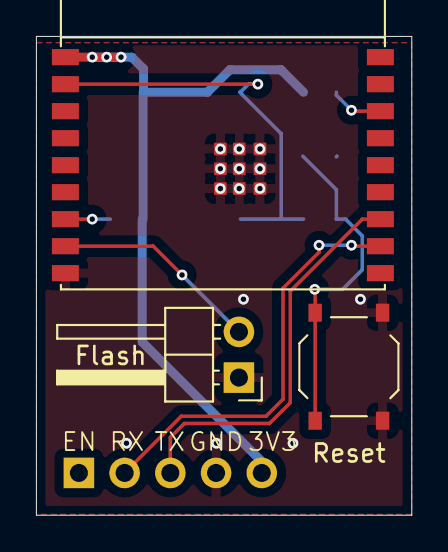
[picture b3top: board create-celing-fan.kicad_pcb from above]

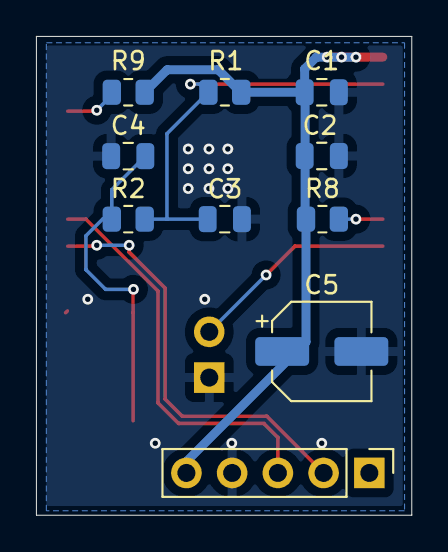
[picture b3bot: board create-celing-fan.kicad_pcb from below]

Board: 2 copper layers, 20.8 x 26.6 mm, 13 parts (10 on the bottom side), 9 nets.

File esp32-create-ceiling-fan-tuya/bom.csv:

Item #,*Designator,*Qty,Manufacturer,*Mfg Part #,Description / Value,*Package/Footprint,Type,Your Instructions / Notes
1,C1,1,Samsung Electro-Mechanics,CL21B106KOQNNNE,10uF,0805,SMD,https://www.lcsc.com/product-detail/C95841.html
2,"C2,C4",2,Samsung Electro-Mechanics,CL21B104KBCNNNC,0.1uF,0805,SMD,https://www.lcsc.com/product-detail/C1711.html
3,C3,1,Samsung Electro-Mechanics,CL21B105KBFNNNE,1uF,0805,SMD,https://www.lcsc.com/product-detail/C28323.html
4,C5,1,FOSAN,FVH010ADA101M0554,100uF ±20% 10V Aluminum Electrolytic Capacitors,5x5.4,SMD,https://www.lcsc.com/product-detail/C7469983.html
5,J1,1,JXTCONN,PM2.54-1X5PM-H85,"3A 5P Through Hole -40℃~+105℃ 8.5mm 1x5P 2.54mm Top 1 Square Hole Through Hole,P=2.54mm Headers, Receptacles, Female Sockets RoHS",P=2.54mm,Through Hole,https://www.lcsc.com/product-detail/C42431843.html
6,"R1,R8,R9",3,FOJAN,FRC0805F1002TS,10kOm,0805,SMD,https://www.lcsc.com/product-detail/C2907219.html
7,R2,1,FOJAN,FRC0805P000 TS,0Om,0805,SMD,https://www.lcsc.com/product-detail/C2907288.html
8,SW1,1,XKB Connection,TS-1187A-B-A-B,Tactile Switch SPST 160gf 1.5mm 5.1mm x 5.1mm Surface Mount,"SMD-4P,5.1x5.1mm",SMD,https://www.lcsc.com/product-detail/C318884.html
9,SW2,1,hanxia,HX PZ2.54-1x2P WZ,"Pin Header 2 Position 2.54mm Pitch Single Row Through Hole, Right Angle -40℃~+105℃",P=2.54mm,Through Hole,https://www.lcsc.com/product-detail/C32713261.html
10,U1,1,ESPRESSIF,ESP32-C3-WROOM-02-N4,2.4GHz ESP32-C3 Chip On-board PCB Antenna -105dBm VFQFN-32-EP RF Transceiver Modules and Modems RoHS,VFQFN-32-EP,SMD,https://www.lcsc.com/product-detail/C2934560.html

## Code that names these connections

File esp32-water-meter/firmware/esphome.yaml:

# Work in progress. Targets the custom water-meter board; see README.md.

substitutions:
  pulse_debounce: "200ms"
  liters_per_pulse: "1"
  persist_coalesce: "15s"
  charger_debounce: "2s"

packages:
  common: !include common-wifi.yaml

esphome:
  name: water-meter
  friendly_name: "Water Meter"
  includes:
    - usb_dp.h
  on_boot:
    - priority: 800
      then:
        - lambda: "usb_dp_pullup(false);"
    - priority: -100
      then:
        - component.update: total_detections
        - component.update: current_ticks

esp32:
  board: esp32-c6-devkitc-1
  variant: esp32c6
  flash_size: 8MB
  framework:
    type: esp-idf
    sdkconfig_options:
      CONFIG_PM_ENABLE: y
      CONFIG_PM_DFS_INIT_AUTO: y

logger:
  hardware_uart: UART0

api:
  encryption:
    key: !secret water_meter_api_encryption_key

ota:
  - platform: esphome
    password: !secret water_meter_ota_password

preferences:
  flash_write_interval: 60s

globals:
  - id: tick_count
    type: int
    restore_value: yes
    initial_value: "0"

script:
  - id: persist_counter
    mode: single
    then:
      - delay: ${persist_coalesce}
      - lambda: "global_preferences->sync();"

switch:
  - platform: gpio
    pin: GPIO7
    id: battery_charger
    name: "Battery Charger"
    icon: "mdi:battery-charging"
    entity_category: config
    restore_mode: ALWAYS_ON
    inverted: true

  - platform: gpio
    pin: GPIO21
    id: power_led
    name: "Power LED"
    icon: "mdi:led-on"
    entity_category: config
    restore_mode: ALWAYS_ON
    inverted: true

number:
  - platform: template
    id: base_value
    name: "Initial Reading"
    icon: "mdi:counter"
    entity_category: config
    unit_of_measurement: "m³"
    device_class: water
    mode: box
    optimistic: true
    min_value: 0
    max_value: 1000000
    step: 0.001
    restore_value: yes
    initial_value: 0
    on_value:
      then:
        - component.update: total_detections

sensor:
  - platform: adc
    pin: GPIO2
    id: battery_voltage
    name: "Battery Voltage"
    icon: "mdi:battery"
    device_class: voltage
    state_class: measurement
    entity_category: diagnostic
    attenuation: 12db
    unit_of_measurement: "V"
    accuracy_decimals: 2
    update_interval: 30s
    filters:
      - median:
          window_size: 5
          send_every: 1
          send_first_at: 1
      - multiply: 2.0

  - platform: template
    id: total_detections
    name: "Total Water"
    icon: "mdi:water"
    device_class: water
    state_class: total_increasing
    unit_of_measurement: "m³"
    accuracy_decimals: 3
    lambda: "return id(base_value).state + id(tick_count) * ${liters_per_pulse} / 1000.0;"
    update_interval: never

  - platform: template
    id: current_ticks
    name: "Since Reset"
    icon: "mdi:counter"
    device_class: water
    state_class: total_increasing
    entity_category: diagnostic
    unit_of_measurement: "L"
    accuracy_decimals: 0
    lambda: "return id(tick_count) * ${liters_per_pulse};"
    update_interval: never

binary_sensor:
  - platform: gpio
    pin: GPIO6
    id: usb_power_connected
    name: "USB Power Connected"
    icon: "mdi:usb-port"
    device_class: plug
    entity_category: diagnostic
    filters:
      - delayed_on: 50ms
      - delayed_off: 50ms
    on_press:
      then:
        - lambda: "usb_dp_pullup(true);"
    on_release:
      then:
        - lambda: "usb_dp_pullup(false);"

  - platform: gpio
    id: chrg_stdby
    internal: true
    pin:
      number: GPIO22
      inverted: true
      mode:
        input: true
        pullup: true
    filters:
      - delayed_on_off: ${charger_debounce}
    on_state:
      then:
        - component.update: charger_status

  - platform: gpio
    id: chrg_ch
    internal: true
    pin:
      number: GPIO23
      inverted: true
      mode:
        input: true
        pullup: true
    filters:
      - delayed_on_off: ${charger_debounce}
    on_state:
      then:
        - component.update: charger_status

  - platform: gpio
    id: proximity_trigger
    internal: true
    pin:
      number: GPIO5
      inverted: true
      ignore_strapping_warning: true
      mode:
        input: true
        pullup: true
    filters:
      - delayed_on_off: ${pulse_debounce}
    on_press:
      then:
        - lambda: "id(tick_count) += 1;"
        - component.update: total_detections
        - component.update: current_ticks
        - script.execute: persist_counter

text_sensor:
  - platform: template
    id: charger_status
    name: "Charger Status"
    icon: "mdi:battery-charging"
    entity_category: diagnostic
    update_interval: 60s
    lambda: |-
      const bool charging = id(chrg_ch).state;
      const bool full = id(chrg_stdby).state;
      const char *out;
      if (charging && full) { out = "Fault"; }
      else if (charging)    { out = "Charging"; }
      else if (full)        { out = "Full"; }
      else                  { out = "Idle"; }
      // update() publishes unconditionally, so suppress no-op republishes here.
      if (id(charger_status).state == out) return {};
      return {out};

button:
  - platform: template
    id: reset_ticks
    name: "Reset Ticks to Zero"
    icon: "mdi:restart"
    entity_category: config
    on_press:
      then:
        - lambda: "id(tick_count) = 0;"
        - component.update: total_detections
        - component.update: current_ticks
        - lambda: "global_preferences->sync();"

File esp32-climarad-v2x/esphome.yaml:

# SPDX-License-Identifier: PolyForm-Noncommercial-1.0.0
# Required Notice: Copyright (c) 2025-2026 Ivan Kruglov
# License: https://polyformproject.org/licenses/noncommercial/1.0.0

substitutions:
  id_prefix: climarad_sensa_v2x
  name_prefix: "ClimaRad Sensa V2X"

esphome:
  name: climarad-sensa-v2x-modbus
  friendly_name: "Climarad Sensa V2X"

esp32:
  board: esp32-s3-devkitc-1
  variant: esp32s3
  flash_size: 16MB
  framework:
    type: esp-idf

logger:
  level: INFO

# sync time with home assistant
time:
  - platform: homeassistant
    id: homeassistant_time

api:

ota:
  - platform: esphome

ethernet:
  type: W5500
  clk_pin: GPIO13
  mosi_pin: GPIO11
  miso_pin: GPIO12
  cs_pin: GPIO14
  interrupt_pin: GPIO10
  reset_pin: GPIO9

uart:
  id: uart_modbus
  tx_pin: GPIO17  # pin 34
  rx_pin: GPIO21  # pin 35
  baud_rate: 9600
  stop_bits: 1
  parity: EVEN

modbus:
  id: climarad_modbus
  role: client
  send_wait_time: 500ms

modbus_controller:
  - id: climarad_sensa_v2x
    modbus_id: climarad_modbus
    address: 000  # TODO: Modbus Slave ID is written on Climarad Modbus module cable
    update_interval: 60s
    command_throttle: 500ms

sensor:
  - platform: modbus_controller
    modbus_controller_id: climarad_sensa_v2x
    name: "${name_prefix} CO2"
    id: "${id_prefix}_co2"
    register_type: read
    address: 0x0000
    value_type: S_WORD
    state_class: measurement
    device_class: carbon_dioxide
    unit_of_measurement: ppm
    filters:
      - filter_out: 32767 # specific value which climarad use during manual modes
      - filter_out: 0
      - clamp:
          min_value: 1
          max_value: 5000
          ignore_out_of_range: true

  - platform: modbus_controller
    modbus_controller_id: climarad_sensa_v2x
    name: "${name_prefix} Humidity"
    id: "${id_prefix}_humidity"
    register_type: read
    address: 0x0002
    value_type: S_WORD
    state_class: measurement
    device_class: humidity
    unit_of_measurement: '%'
    filters:
      - multiply: 0.1
      - clamp:
          min_value: 0.0
          max_value: 100.0
          ignore_out_of_range: true
    accuracy_decimals: 1

  - platform: modbus_controller
    modbus_controller_id: climarad_sensa_v2x
    name: "${name_prefix} Temperature"
    id: "${id_prefix}_temperature"
    register_type: read
    address: 0x0004
    value_type: S_WORD
    state_class: measurement
    device_class: temperature
    unit_of_measurement: '°C'
    filters:
      - multiply: 0.01
      - clamp:
          min_value: -50.00
          max_value: 50.00
          ignore_out_of_range: true
    accuracy_decimals: 2

    ######################
    # Diagnostic sensors #
    ######################

  - platform: modbus_controller
    modbus_controller_id: climarad_sensa_v2x
    name: "${name_prefix} Desired CO2"
    id: "${id_prefix}_desired_co2"
    register_type: read
    address: 0x0001
    value_type: S_WORD
    state_class: measurement
    device_class: carbon_dioxide
    unit_of_measurement: ppm
    entity_category: diagnostic

  - platform: modbus_controller
    modbus_controller_id: climarad_sensa_v2x
    name: "${name_prefix} Fan Speed Air Supply"
    id: "${id_prefix}_fan_speed_air_supply"
    register_type: read
    address: 0x000B
    value_type: U_WORD
    state_class: measurement
    unit_of_measurement: rpm
    entity_category: diagnostic
    filters:
      - clamp:
          min_value: 0
          max_value: 5000
          ignore_out_of_range: true

  - platform: modbus_controller
    modbus_controller_id: climarad_sensa_v2x
    name: "${name_prefix} Fan Speed Air Exhaust"
    id: "${id_prefix}_fan_speed_air_exhaust"
    register_type: read
    address: 0x000C
    value_type: U_WORD
    state_class: measurement
    unit_of_measurement: rpm
    entity_category: diagnostic
    filters:
      - clamp:
          min_value: 0
          max_value: 5000
          ignore_out_of_range: true

  - platform: modbus_controller
    modbus_controller_id: climarad_sensa_v2x
    name: "${name_prefix} Number of Times Filter Counter Reset"
    id: "${id_prefix}_number_of_times_filter_counter_reset"
    register_type: read
    address: 0x000D
    value_type: U_WORD
    state_class: measurement
    entity_category: diagnostic

text_sensor:
  - platform: modbus_controller
    modbus_controller_id: climarad_sensa_v2x
    name: "${name_prefix} Current Mode"
    id: "${id_prefix}_current_mode"
    register_type: read
    address: 0x0005
    entity_category: diagnostic
    raw_encode: HEXBYTES
    lambda: |-
      uint16_t value = modbus_controller::word_from_hex_str(x, 0);
      switch (value) {
        case 0: return std::string("Auto");
        case 1: return std::string("Pause");
        case 2: return std::string("High");
        case 3: return std::string("Maximal");
        case 4: return std::string("Summer night");
        case 5: return std::string("5-position ventilation");
        case 6: return std::string("5-position recirculation");
        default: return std::string("Unknown");
      }

  - platform: modbus_controller
    modbus_controller_id: climarad_sensa_v2x
    name: "${name_prefix} Error"
    id: "${id_prefix}_error"
    register_type: read
    address: 0x000F
    entity_category: diagnostic
    raw_encode: HEXBYTES
    lambda: |-
      uint16_t value = modbus_controller::word_from_hex_str(x, 0);

      std::string result;
      if (value & 1)
        result += "Outside Temperature,";
      if (value & 2)
        result += "Inside Temperature,";
      if (value & 4)
        result += "Air Quality,";
      if (value & 8)
        result += "Humidity,";
      if (value & 16)
        result += "Supply Fan,";
      if (value & 32)
        result += "Exhaust Fan,";
      if (value & 64)
        result += "Power Supply Fan,";
      if (value & 128)
        result += "Fan Speed,";
      if (value & 256)
        result += "RF,";
      if (value & 512)
        result += "RF Sensor,";

      if (result.ends_with(','))
        result.pop_back();

      return result.empty() ? "None" : result;

select:
  - platform: modbus_controller
    modbus_controller_id: climarad_sensa_v2x
    name: "${name_prefix} Desired CO2 Level"
    id: "${id_prefix}_desired_co2_level"
    address: 0x101D
    value_type: U_WORD
    optionsmap:
      "1200PPM": 0
      "1000PPM": 1
      "800PPM": 2
      "600PPM": 3
      "400PPM": 4
    entity_category: config

  - platform: modbus_controller
    modbus_controller_id: climarad_sensa_v2x
    name: "${name_prefix} Desired Mode"
    id: "${id_prefix}_desired_mode"
    address: 0x1005
    value_type: U_WORD
    optionsmap:
      "Auto": 0
      "Pause": 1
      "High": 2
      "Maximal": 3
      "Summer night": 4
      "5-position ventilation": 5
      "5-position recirculation": 6
    entity_category: config

  - platform: modbus_controller
    modbus_controller_id: climarad_sensa_v2x
    name: "${name_prefix} Child Lock"
    id: "${id_prefix}_child_lock"
    address: 0x1026
    value_type: U_WORD
    optionsmap:
      "Off": 0
      "On": 1
    entity_category: config

  - platform: modbus_controller
    modbus_controller_id: climarad_sensa_v2x
    name: "${name_prefix} Window Ventilation"
    id: "${id_prefix}_window_ventilation"
    address: 0x103E
    value_type: U_WORD
    optionsmap:
      "Absent": 0
      "Present": 1
    entity_category: config

number:
  - platform: modbus_controller
    modbus_controller_id: climarad_sensa_v2x
    name: "${name_prefix} CO2 Compensation"
    id: "${id_prefix}_co2_compensation"
    register_type: holding
    address: 0x1000
    value_type: S_WORD
    entity_category: config
    unit_of_measurement: ppm
    device_class: carbon_dioxide
    mode: box

  - platform: modbus_controller
    modbus_controller_id: climarad_sensa_v2x
    name: "${name_prefix} LED Brightness"
    id: "${id_prefix}_led_brightness"
    register_type: holding
    address: 0x1027
    value_type: U_WORD
    min_value: 0
    max_value: 5
    entity_category: config
    mode: slider

button:
  - platform: restart
    name: "Restart"
